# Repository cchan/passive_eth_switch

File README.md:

# passive_eth_switch

Unpowered ethernet switch, using only diodes.

All based on [this extremely clever design](http://www.zen22142.zen.co.uk/Circuits/Interface/pethhub.htm).

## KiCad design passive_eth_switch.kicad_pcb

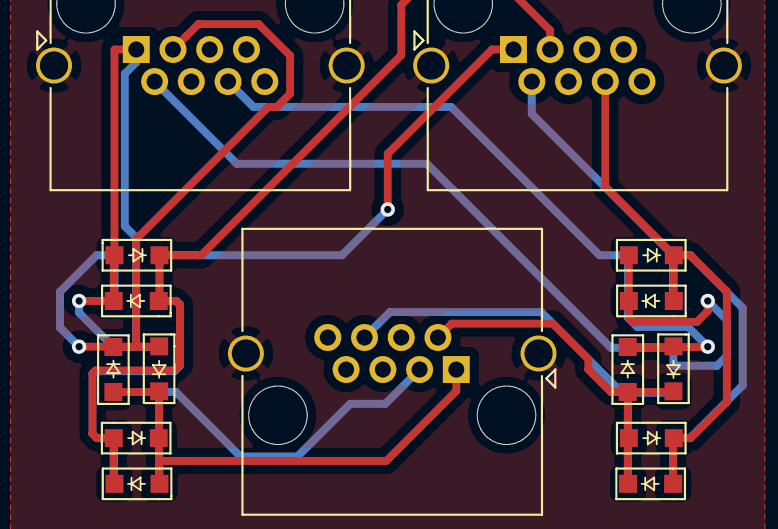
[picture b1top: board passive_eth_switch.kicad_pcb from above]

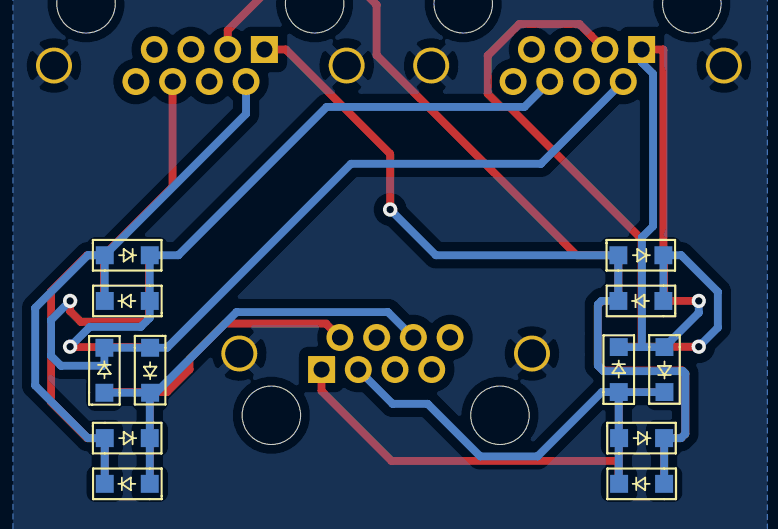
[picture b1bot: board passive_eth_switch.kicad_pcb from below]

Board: 2 copper layers, 27 parts (12 on the bottom side), 13 nets.

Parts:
D1, D2, D3, D4, D5, D6, D7, D8, D9, D10, D11, D12, D13, D14, D15, D16, D17, D18, D19, D20, D21, D22, D23, D24: D; D_SOD-323_HandSoldering_CustomSilk
JA1: RJ45_Shielded; RJ45_Amphenol_RJHSE5380
JB1: RJ45_Shielded; RJ45_Amphenol_RJHSE5380
JC1: RJ45_Shielded; RJ45_Amphenol_RJHSE5380

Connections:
A1: D1.1, D4.2, D7.1, D10.2, JA1.1
A2: D13.1, D16.2, D19.1, D22.2, JA1.2
A3: D3.2, D6.1, D9.2, D12.1, JA1.3
A6: D15.2, D18.1, D21.2, D24.1, JA1.6
B1: D2.2, D3.1, D5.1, D6.2, JB1.1
B2: D14.2, D15.1, D17.1, D18.2, JB1.2
B3: D7.2, D8.1, D10.1, D11.2, JB1.3
B6: D19.2, D20.1, D22.1, D23.2, JB1.6
C1: D8.2, D9.1, D11.1, D12.2, JC1.1
C2: D20.2, D21.1, D23.1, D24.2, JC1.2
C3: D1.2, D2.1, D4.1, D5.2, JC1.3
C6: D13.2, D14.1, D16.1, D17.2, JC1.6
GND: JA1.SH, JB1.SH, JC1.SH

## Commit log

2020-01-31 v0.1 sent for printing
2020-01-31 move trace to not intersect logo
2020-01-31 fix readme
